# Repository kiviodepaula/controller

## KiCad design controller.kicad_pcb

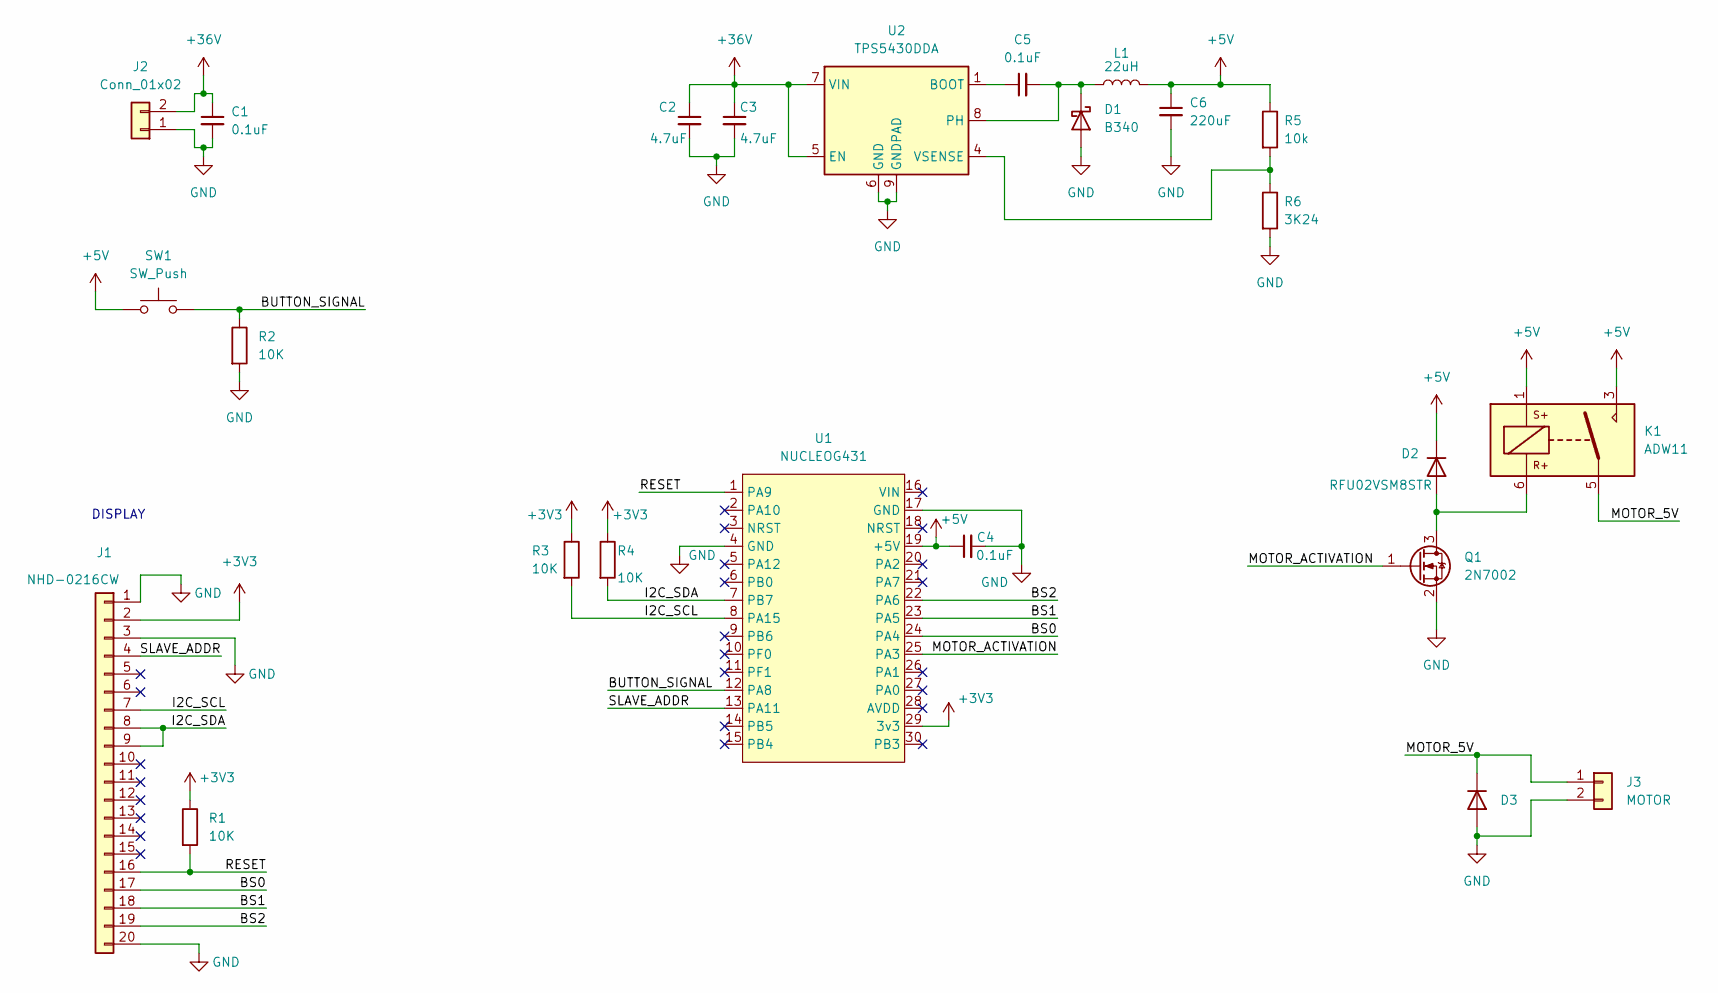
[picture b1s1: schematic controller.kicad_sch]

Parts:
C1, C4, C5: 0.1uF; C_0603_1608Metric_Pad1.08x0.95mm_HandSolder
C2, C3: 4.7uF; C_1206_3216Metric_Pad1.33x1.80mm_HandSolder
C6: 220uF; CP_Elec_8x6.9
D1: B340; D_SMC
D2: RFU02VSM8STR; D_TUMD2
D3: RB168VYM150FHTR; D_TUMD2
J1: NHD-0216CW; NHD-0216CW-AB3
J2: Conn_01x02; PinSocket_1x02_P2.54mm_Vertical
J3: MOTOR; PinSocket_1x02_P2.54mm_Vertical
K1: ADW11; Relay_1P1T_NO_10x24x18.8mm_Panasonic_ADW11xxxxW_THT
L1: 22uH; SRR1208-220ML
Q1: 2N7002; SOT-23
R1, R2, R3, R4: 10K; R_0805_2012Metric_Pad1.20x1.40mm_HandSolder
R5: 10k; R_0805_2012Metric_Pad1.20x1.40mm_HandSolder
R6: 3K24; R_0805_2012Metric_Pad1.20x1.40mm_HandSolder
SW1: SW_Push; SW_PUSH_6mm
U1: NUCLEOG431; Nucleog4
U2: TPS5430DDA; TI_SO-PowerPAD-8_ThermalVias

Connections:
+3V3: J1.2, R1.1, R3.1, R4.1, U1.29 (3v3)
+5V: C4.1, C6.1, D2.1 (K), K1.1, K1.3, L1.2, R5.1, SW1.1, U1.19 (+5V)
+36V: C1.1, C2.1, C3.1, J2.2, U2.5 (EN), U2.7 (VIN)
/BS0: J1.17, U1.24 (PA4)
/BS1: J1.18, U1.23 (PA5)
/BS2: J1.19, U1.22 (PA6)
/BUTTON_SIGNAL: R2.1, SW1.2, U1.12 (PA8)
/I2C_SCL: J1.7, R3.2, U1.8 (PA15)
/I2C_SDA: J1.8, J1.9, R4.2, U1.7 (PB7)
/MOTOR_5V: D3.1 (K), J3.1, K1.5
/MOTOR_ACTIVATION: Q1.1 (G), U1.25 (PA3)
/RESET: J1.16, R1.2, U1.1 (PA9)
/SLAVE_ADDR: J1.4, U1.13 (PA11)
GND: C1.2, C2.2, C3.2, C4.2, C6.2, D1.2 (A), D3.2 (A), J1.1, J1.3, J1.20, J2.1, J3.2, Q1.2 (S), R2.2, R6.2, U1.4 (GND), U1.17 (GND), U2.6 (GND), U2.9 (GNDPAD)
unnamed: C5.1, U2.1 (BOOT)
unnamed: C5.2, D1.1 (K), L1.1, U2.8 (PH)
unnamed: D2.2 (A), K1.6, Q1.3 (D)
unnamed: R5.2, R6.1, U2.4 (VSENSE)

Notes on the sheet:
DISPLAY

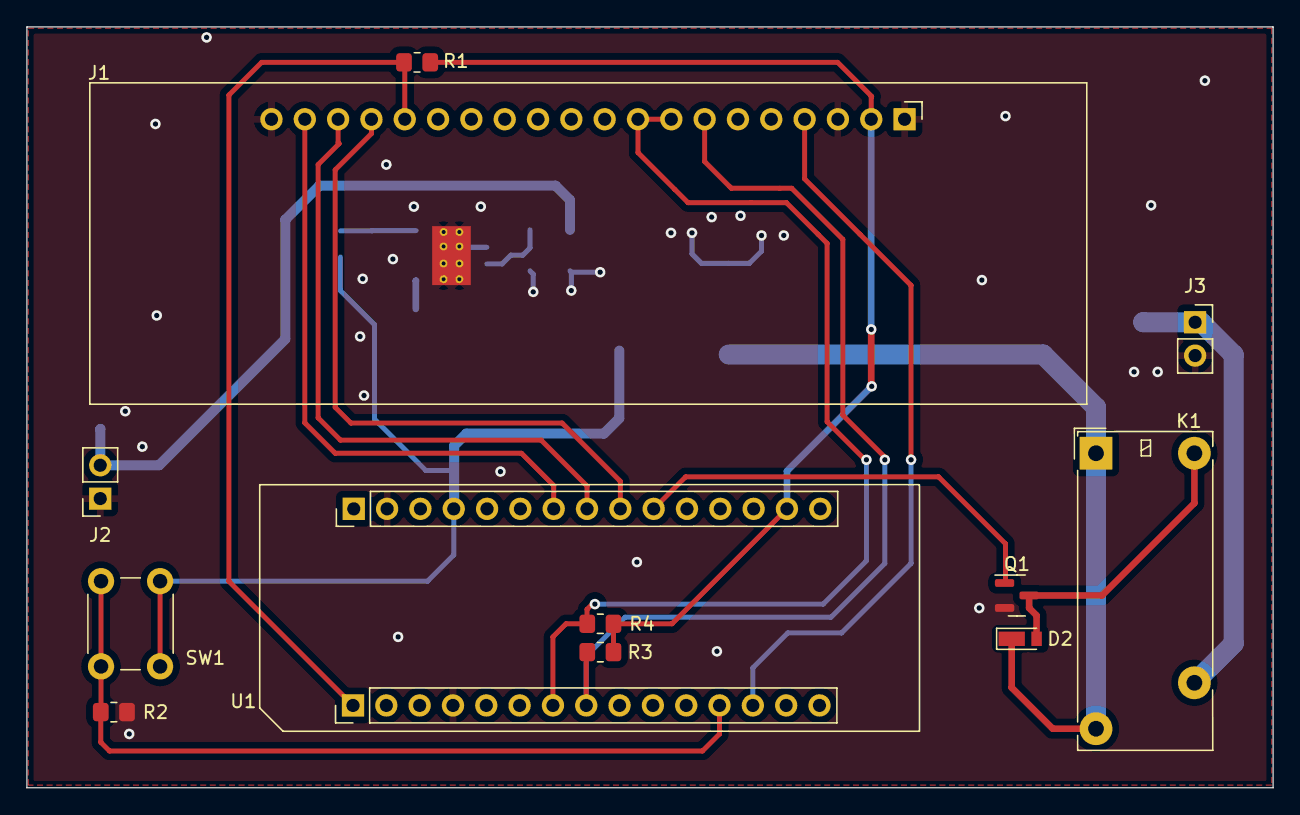
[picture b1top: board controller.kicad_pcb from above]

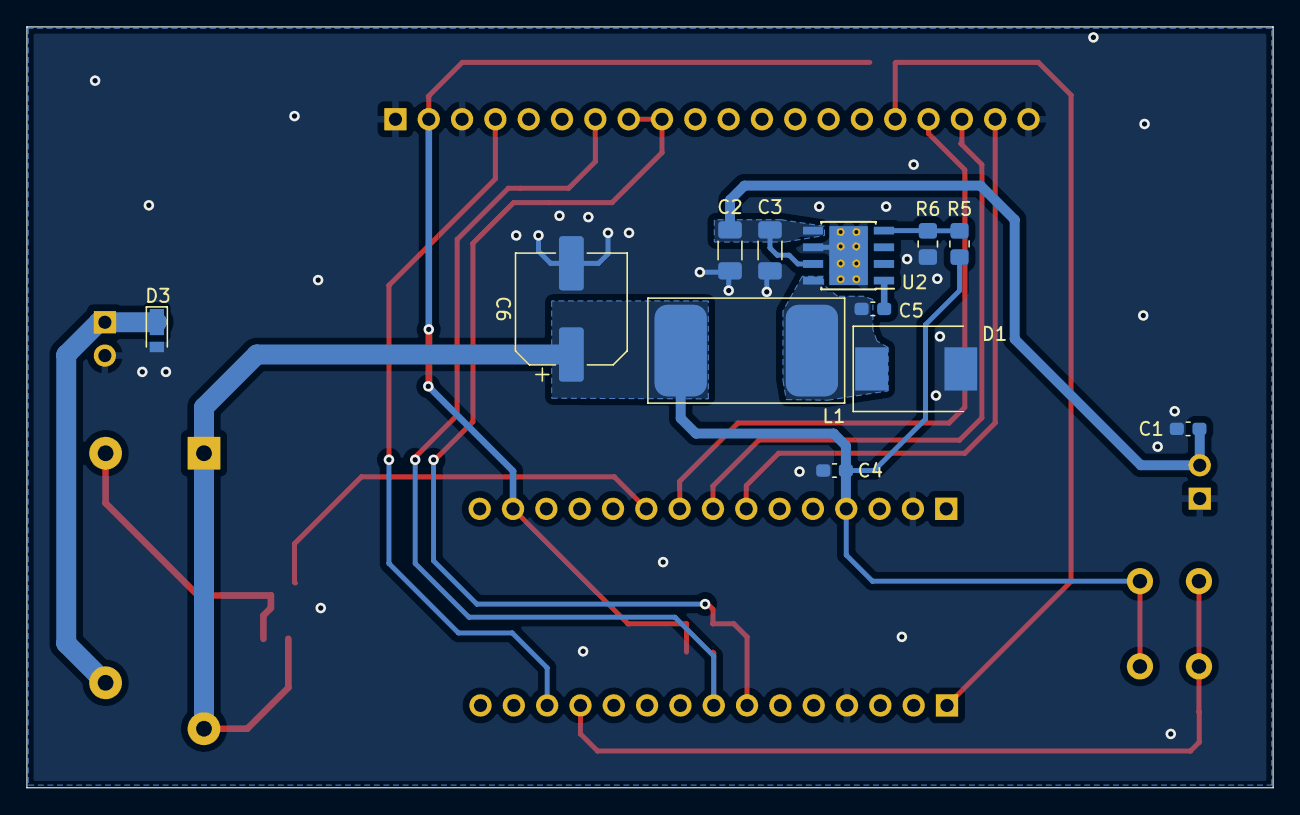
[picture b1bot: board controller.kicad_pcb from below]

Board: 2 copper layers, 95.0 x 58.0 mm, 24 parts (12 on the bottom side), 18 nets.

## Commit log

2023-11-07 add fabrication files
